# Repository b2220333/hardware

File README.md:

This repository contains information and documentation about the hardware platforms
used and supported in the micro-ROS project.

### Reference hardware platform and development board
The reference hardware platform for the micro-ROS project is the STMicroelectronics
STM32F4 series of microcontrollers. Particularly, the reference development board is the
`Olimex LTD STM32-E407`. More information about this development board can be found in the
[Olimex LTD STM32-E407 instructions](documentation/stm32-e407/stm32-e407.md) file.

### Supporting a new board
TODO: provide instructions on how one should proceed to get a new board supported.

### Other boards (*work in progress (WIP)* )

- **ultra low resources**:
   - STM32VLDISCOVERY (STM32F1)
   - STM32L-DISCOVERY (STM32F4L1)
   - Nucleo-64 (STM32F103)
   - Nucleo-64 (STM32L152)
- **low resources**:
   - *None for now*
- **safety-compliant**:
   - Texas Instruments LAUNCHXL-TMS57004

### License
Unless specified, the content and material available here is open source and
licensed under `<include consortium license>`.

### Conflicts of interest
*The authors declare that there's no conflict of interest in connexion
to the hardware platforms supported or recommended. The same applies to Electronic
Design Automation (EDA) tools and applications used. In addition, the
authors declare that they have not granted, sought, attempted to obtain or accepted
and will not grant, seek, attempt to obtain, or accept any advantage, financial or
in kind, to or from any party whatsoever, constituting an illegal or corrupt practice,
either directly or indirectly, as an incentive or reward relating to the scope of the
work presented in this repository and its relationship with the micro-ROS project.*

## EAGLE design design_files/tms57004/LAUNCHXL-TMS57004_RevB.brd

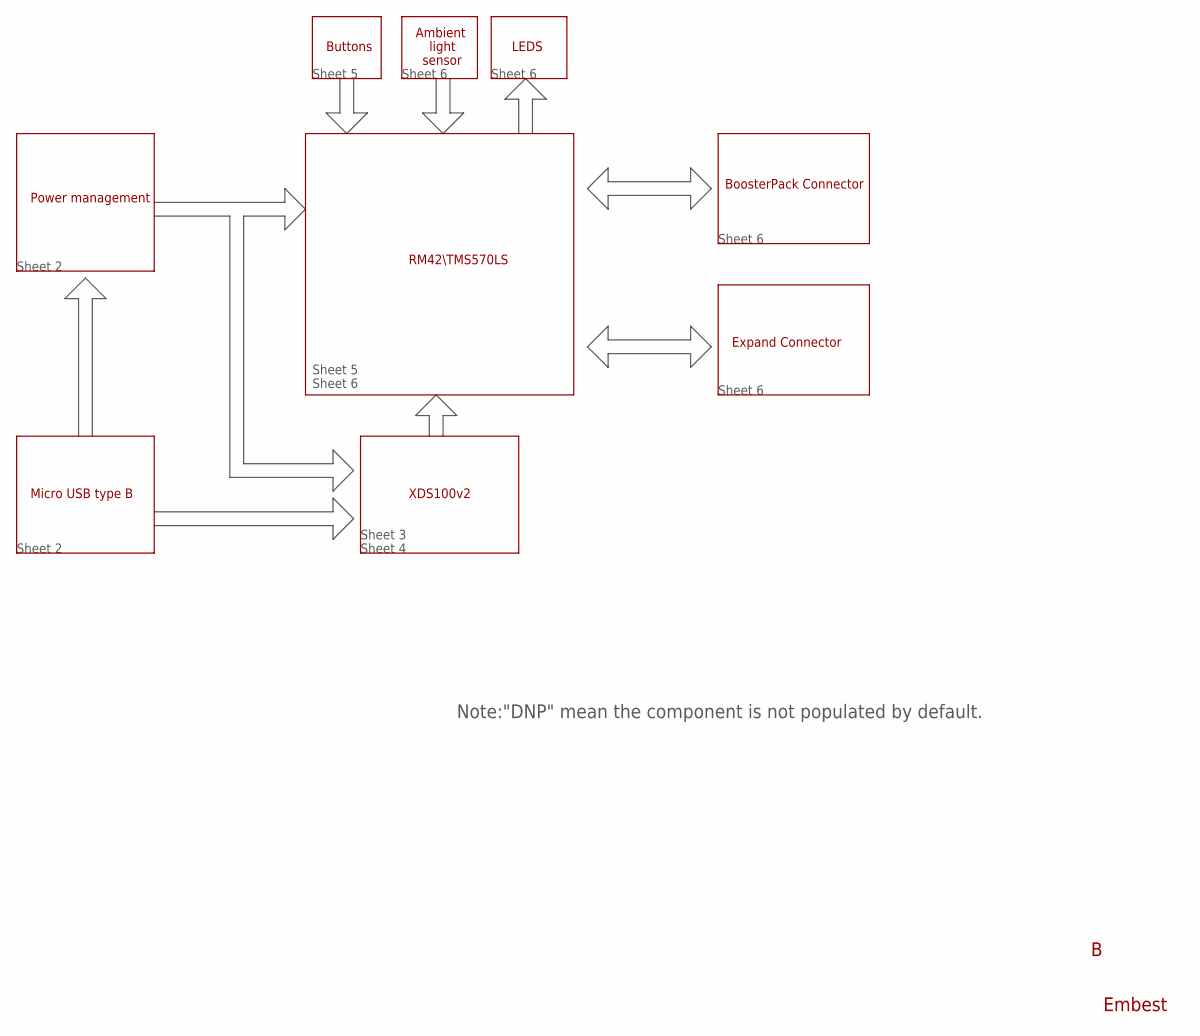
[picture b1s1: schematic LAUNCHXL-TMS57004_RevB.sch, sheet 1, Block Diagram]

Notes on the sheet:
Embest
Power management
Micro USB type B
XDS100v2
RM42\\TMS570LS
BoosterPack Connector
Expand Connector
LEDS
Buttons
Ambient
light
sensor
Note:"DNP" mean the component is not populated by default.
Sheet 2
Sheet 5
Sheet 6
Sheet 3
Sheet 4

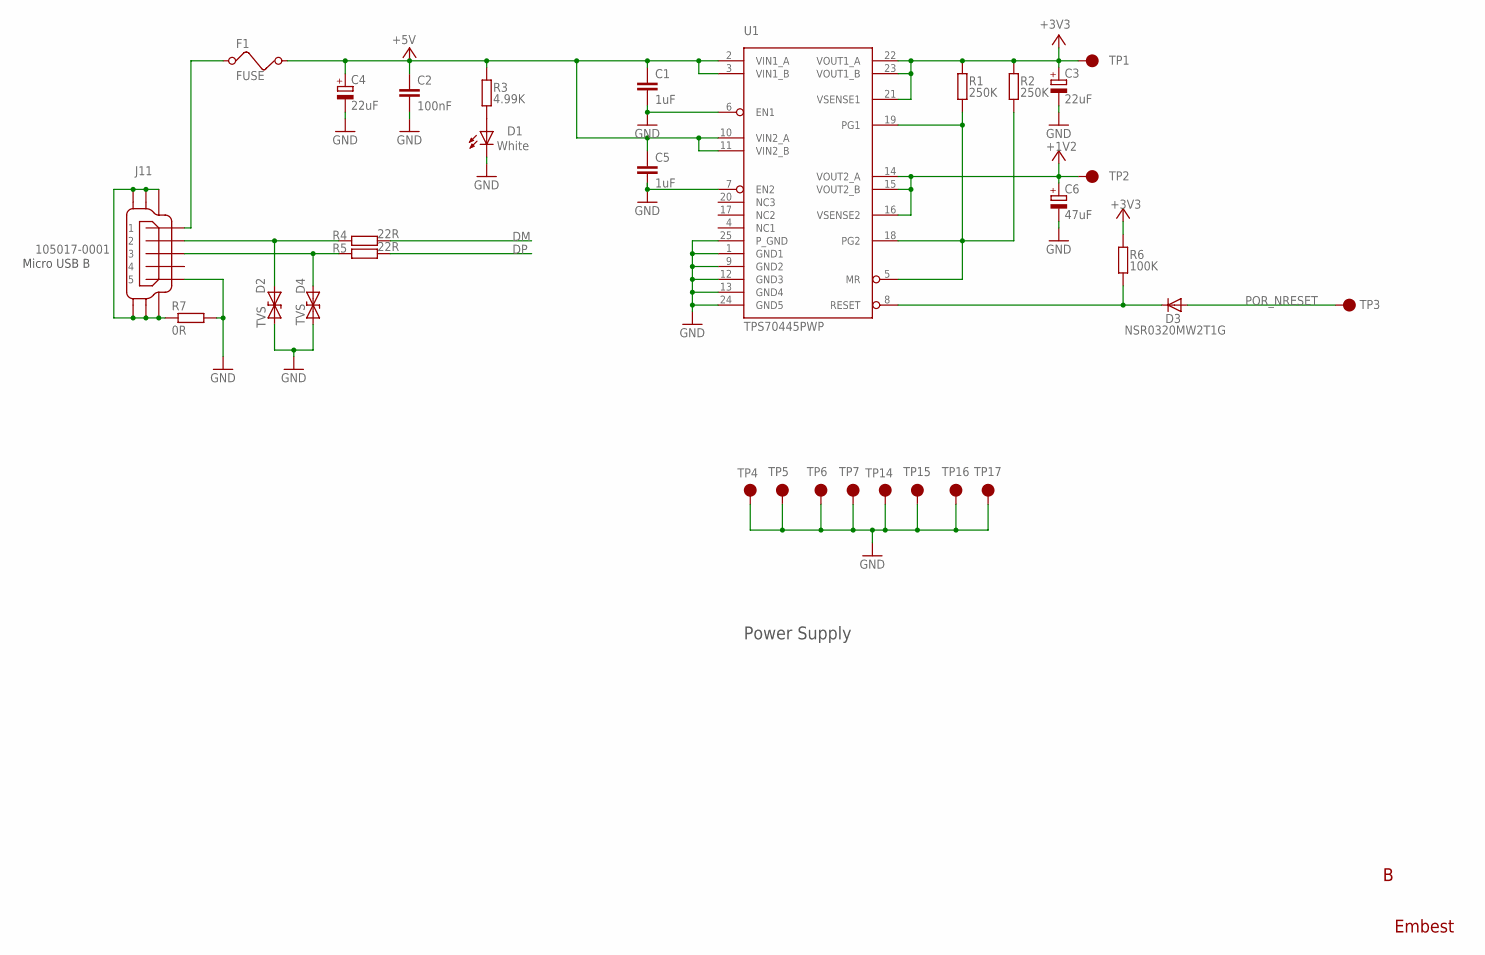
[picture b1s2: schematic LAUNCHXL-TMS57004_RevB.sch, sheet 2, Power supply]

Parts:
C1, C5: 1uF; 0603
C2: 100nF; 0402
C3, C4: 22uF; CT3528
C6: 47uF; CT3528
D1: White; LED0805
D2, D4: TVS; 0402
D3: NSR0320MW2T1G; SOD-323
F1: FUSE; 0805
J11: 105017-0001; MICRO_USB
R1, R2: 250K; 0402
R3: 4.99K; 0402
R4, R5: 22R; 0402
R6: 100K; 0402
R7: 0R; 0603
TP1, TP2, TP3, TP4, TP5, TP6, TP7, TP14, TP15, TP16, TP17: TP
U1: TPS70445PWP; TSSOP24

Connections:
1A: F1.1, J11.1
+3V3: C3.+, R1.2, R2.2, R6.2, TP1.1, U1.21 (VSENSE1), U1.22 (VOUT1_A), U1.23 (VOUT1_B); also elsewhere on the board
+5V: C1.1, C2.1, C4.+, C5.1, F1.2, R3.2, U1.2 (VIN1_A), U1.3 (VIN1_B), U1.10 (VIN2_A), U1.11 (VIN2_B); also elsewhere on the board
DM: R4.1; also elsewhere on the board
DP: R5.1; also elsewhere on the board
GND: C1.2, C2.2, C3.-, C4.-, C5.2, C6.-, D1.C, D2.1, D4.2, J11.5, R7.2, TP4.1, TP5.1, TP6.1, TP7.1, TP14.1, TP15.1, TP16.1, TP17.1, U1.1 (GND1), U1.6 (EN1), U1.7 (EN2), U1.9 (GND2), U1.12 (GND3), U1.13 (GND4), U1.24 (GND5), U1.25 (P_GND); also elsewhere on the board
unnamed: J11.6, J11.7, J11.8, J11.9, J11.10, J11.11, R7.1
unnamed: D2.2, J11.2, R4.2
unnamed: D4.1, J11.3, R5.2
unnamed: D3.C, R6.1, U1.8 (RESET)
unnamed: R1.1, R2.1, U1.5 (MR), U1.18 (PG2), U1.19 (PG1)
unnamed: D1.A, R3.1
POR_NRESET: D3.A, TP3.1; also elsewhere on the board
VCC: C6.+, TP2.1, U1.14 (VOUT2_A), U1.15 (VOUT2_B), U1.16 (VSENSE2); also elsewhere on the board

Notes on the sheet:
Embest
Micro USB B
Power Supply

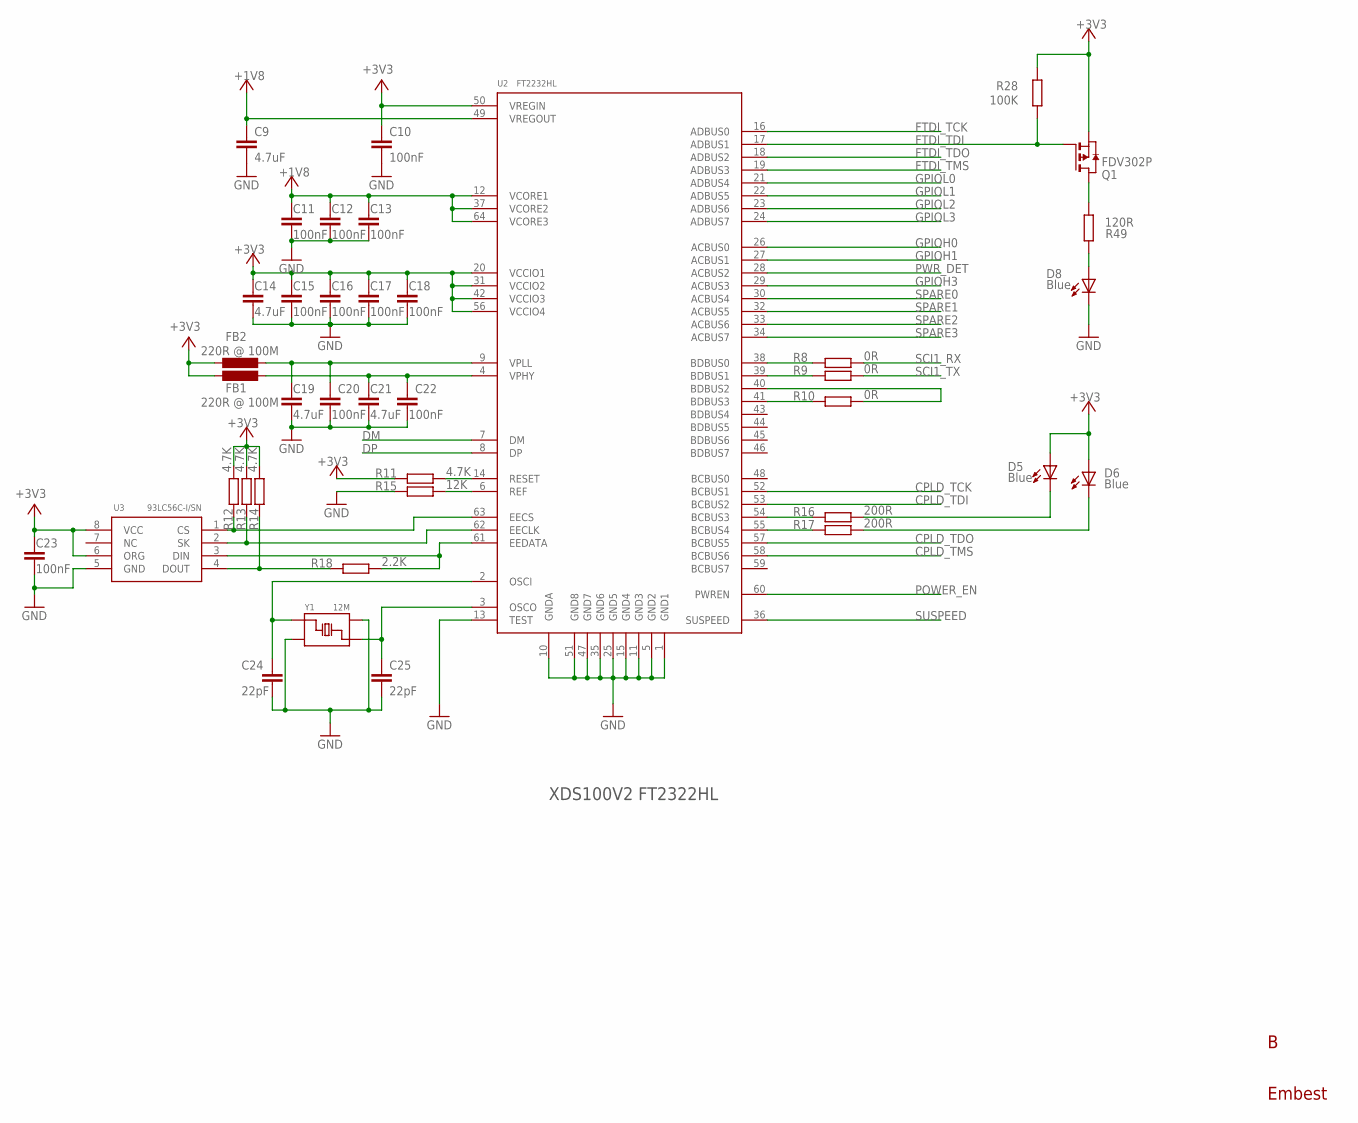
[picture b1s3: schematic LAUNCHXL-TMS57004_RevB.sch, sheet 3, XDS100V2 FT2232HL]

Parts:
C9, C14, C19, C21: 4.7uF; 0805
C10, C11, C12, C13, C15, C16, C17, C18, C20, C22, C23: 100nF; 0402
C24, C25: 22pF; 0402
D5, D6, D8: Blue; LED0805
FB1, FB2: 220R @ 100M; 0805
Q1: FDV302P; SOT-23
R8, R9, R10: 0R; 0402
R11, R12, R13, R14: 4.7K; 0402
R15: 12K; 0402
R16, R17: 200R; 0402
R18: 2.2K; 0402
R28: 100K; 0402
R49: 120R; 0402
U2: FT2232HL; LQFP64
U3: 93LC56C-I/SN; SO8
Y1: 12M; CRYSTAL_3225

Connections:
+1V8: C9.1, C11.1, C12.1, C13.1, U2.12 (VCORE1), U2.37 (VCORE2), U2.49 (VREGOUT), U2.64 (VCORE3); also elsewhere on the board
+3V3: C10.1, C14.1, C15.1, C16.1, C17.1, C18.1, C23.1, D5.A, D6.A, FB1.1, FB2.1, Q1.2 (S), R11.1, R12.2, R13.2, R14.2, R28.2, U2.20 (VCCIO1), U2.31 (VCCIO2), U2.42 (VCCIO3), U2.50 (VREGIN), U2.56 (VCCIO4), U3.6 (ORG), U3.8 (VCC); also elsewhere on the board
CPLD_TCK: U2.52 (BCBUS1); also elsewhere on the board
CPLD_TDI: U2.53 (BCBUS2); also elsewhere on the board
CPLD_TDO: U2.57 (BCBUS5); also elsewhere on the board
CPLD_TMS: U2.58 (BCBUS6); also elsewhere on the board
DM: U2.7 (DM); also elsewhere on the board
DP: U2.8 (DP); also elsewhere on the board
FTDI_TCK: U2.16 (ADBUS0); also elsewhere on the board
FTDI_TDI: Q1.3 (G), R28.1, U2.17 (ADBUS1); also elsewhere on the board
FTDI_TDO: U2.18 (ADBUS2); also elsewhere on the board
FTDI_TMS: U2.19 (ADBUS3); also elsewhere on the board
GND: C9.2, C10.2, C11.2, C12.2, C13.2, C14.2, C15.2, C16.2, C17.2, C18.2, C19.2, C20.2, C21.2, C22.2, C23.2, C24.2, C25.2, D8.C, R15.1, U2.1 (GND1), U2.5 (GND2), U2.10 (GNDA), U2.11 (GND3), U2.13 (TEST), U2.15 (GND4), U2.25 (GND5), U2.35 (GND6), U2.47 (GND7), U2.51 (GND8), U3.5 (GND), Y1.P$2, Y1.P$4; also elsewhere on the board
GPIOH0: U2.26 (ACBUS0); also elsewhere on the board
GPIOH1: U2.27 (ACBUS1); also elsewhere on the board
GPIOH3: U2.29 (ACBUS3); also elsewhere on the board
GPIOL0: U2.21 (ADBUS4); also elsewhere on the board
GPIOL1: U2.22 (ADBUS5); also elsewhere on the board
GPIOL2: U2.23 (ADBUS6); also elsewhere on the board
GPIOL3: U2.24 (ADBUS7); also elsewhere on the board
unnamed: C19.1, C20.1, FB1.2, U2.9 (VPLL)
unnamed: C21.1, C22.1, FB2.2, U2.4 (VPHY)
unnamed: R15.2, U2.6 (REF)
unnamed: R11.2, U2.14 (RESET)
unnamed: C24.1, U2.2 (OSCI), Y1.P$3
unnamed: C25.1, U2.3 (OSCO), Y1.P$1
unnamed: R12.1, U2.63 (EECS), U3.1 (CS)
unnamed: R13.1, U2.62 (EECLK), U3.2 (SK)
unnamed: R18.2, U2.61 (EEDATA), U3.3 (DIN)
unnamed: R14.1, R18.1, U3.4 (DOUT)
unnamed: R8.1, U2.38 (BDBUS0)
unnamed: R9.1, U2.39 (BDBUS1)
unnamed: Q1.1 (D), R49.2
unnamed: D8.A, R49.1
unnamed: R10.2, U2.40 (BDBUS2)
unnamed: R10.1, U2.41 (BDBUS3)
unnamed: D5.C, R16.2
unnamed: D6.C, R17.2
unnamed: R16.1, U2.54 (BCBUS3)
unnamed: R17.1, U2.55 (BCBUS4)
POWER_EN: U2.60 (PWREN); also elsewhere on the board
PWR_DET: U2.28 (ACBUS2); also elsewhere on the board
SCI1_RX: R8.2; also elsewhere on the board
SCI1_TX: R9.2; also elsewhere on the board
SPARE0: U2.30 (ACBUS4); also elsewhere on the board
SPARE1: U2.32 (ACBUS5); also elsewhere on the board
SPARE2: U2.33 (ACBUS6); also elsewhere on the board
SPARE3: U2.34 (ACBUS7); also elsewhere on the board
SUSPEED: U2.36 (SUSPEED); also elsewhere on the board

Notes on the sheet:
Embest
XDS100V2 FT2322HL

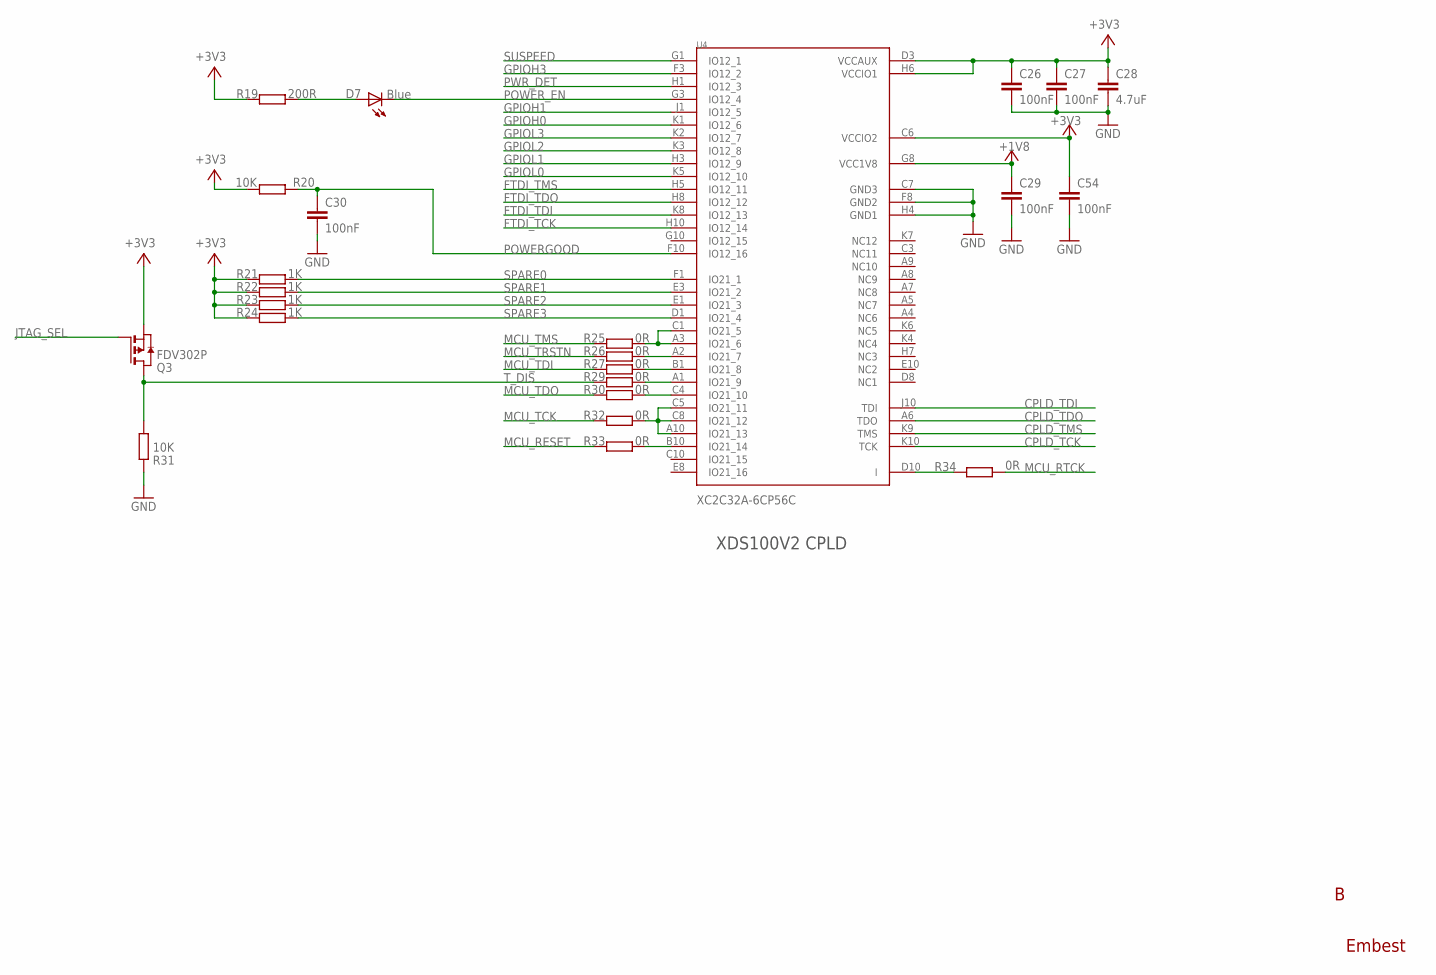
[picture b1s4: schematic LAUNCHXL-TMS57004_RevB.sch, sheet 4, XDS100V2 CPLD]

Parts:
C26, C27, C29, C30, C54: 100nF; 0402
C28: 4.7uF; 0805
D7: Blue; LED0805
Q3: FDV302P; SOT-23
R19: 200R; 0402
R20, R31: 10K; 0402
R21, R22, R23, R24: 1K; 0402
R25, R26, R27, R29, R30, R32, R33, R34: 0R; 0402
U4: XC2C32A-6CP56C; CP56

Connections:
+1V8: C29.1, U4.G8 (VCC1V8); also elsewhere on the board
+3V3: C26.1, C27.1, C28.1, C54.1, Q3.2 (S), R19.1, R20.2, R21.1, R22.1, R23.1, R24.1, U4.C6 (VCCIO2), U4.D3 (VCCAUX), U4.H6 (VCCIO1); also elsewhere on the board
CPLD_TCK: U4.K10 (TCK); also elsewhere on the board
CPLD_TDI: U4.J10 (TDI); also elsewhere on the board
CPLD_TDO: U4.A6 (TDO); also elsewhere on the board
CPLD_TMS: U4.K9 (TMS); also elsewhere on the board
FTDI_TCK: U4.H10 (IO12_14); also elsewhere on the board
FTDI_TDI: U4.K8 (IO12_13); also elsewhere on the board
FTDI_TDO: U4.H8 (IO12_12); also elsewhere on the board
FTDI_TMS: U4.H5 (IO12_11); also elsewhere on the board
GND: C26.2, C27.2, C28.2, C29.2, C30.2, C54.2, R31.1, U4.C7 (GND3), U4.F8 (GND2), U4.H4 (GND1); also elsewhere on the board
GPIOH0: U4.K1 (IO12_6); also elsewhere on the board
GPIOH1: U4.J1 (IO12_5); also elsewhere on the board
GPIOH3: U4.F3 (IO12_2); also elsewhere on the board
GPIOL0: U4.K5 (IO12_10); also elsewhere on the board
GPIOL1: U4.H3 (IO12_9); also elsewhere on the board
GPIOL2: U4.K3 (IO12_8); also elsewhere on the board
GPIOL3: U4.K2 (IO12_7); also elsewhere on the board
JTAG_SEL: Q3.3 (G); also elsewhere on the board
MCU_RESET: R33.1; also elsewhere on the board
MCU_RTCK: R34.2; also elsewhere on the board
MCU_TCK: R32.1; also elsewhere on the board
MCU_TDI: R27.1; also elsewhere on the board
MCU_TDO: R30.1; also elsewhere on the board
MCU_TMS: R25.1; also elsewhere on the board
MCU_TRSTN: R26.1; also elsewhere on the board
unnamed: D7.A, R19.2
unnamed: R25.2, U4.A3 (IO21_6), U4.C1 (IO21_5)
unnamed: R26.2, U4.A2 (IO21_7)
unnamed: R27.2, U4.B1 (IO21_8)
unnamed: R29.2, U4.A1 (IO21_9)
unnamed: R30.2, U4.C4 (IO21_10)
unnamed: R32.2, U4.A10 (IO21_13), U4.C5 (IO21_11), U4.C8 (IO21_12)
unnamed: R33.2, U4.B10 (IO21_14)
unnamed: R34.1, U4.D10 (I)
POWERGOOD: C30.1, R20.1, U4.F10 (IO12_16)
POWER_EN: D7.C, U4.G3 (IO12_4); also elsewhere on the board
PWR_DET: U4.H1 (IO12_3); also elsewhere on the board
SPARE0: R21.2, U4.F1 (IO21_1); also elsewhere on the board
SPARE1: R22.2, U4.E3 (IO21_2); also elsewhere on the board
SPARE2: R23.2, U4.E1 (IO21_3); also elsewhere on the board
SPARE3: R24.2, U4.D1 (IO21_4); also elsewhere on the board
SUSPEED: U4.G1 (IO12_1); also elsewhere on the board
T_DIS: Q3.1 (D), R29.1, R31.2

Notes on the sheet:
Embest
XDS100V2 CPLD

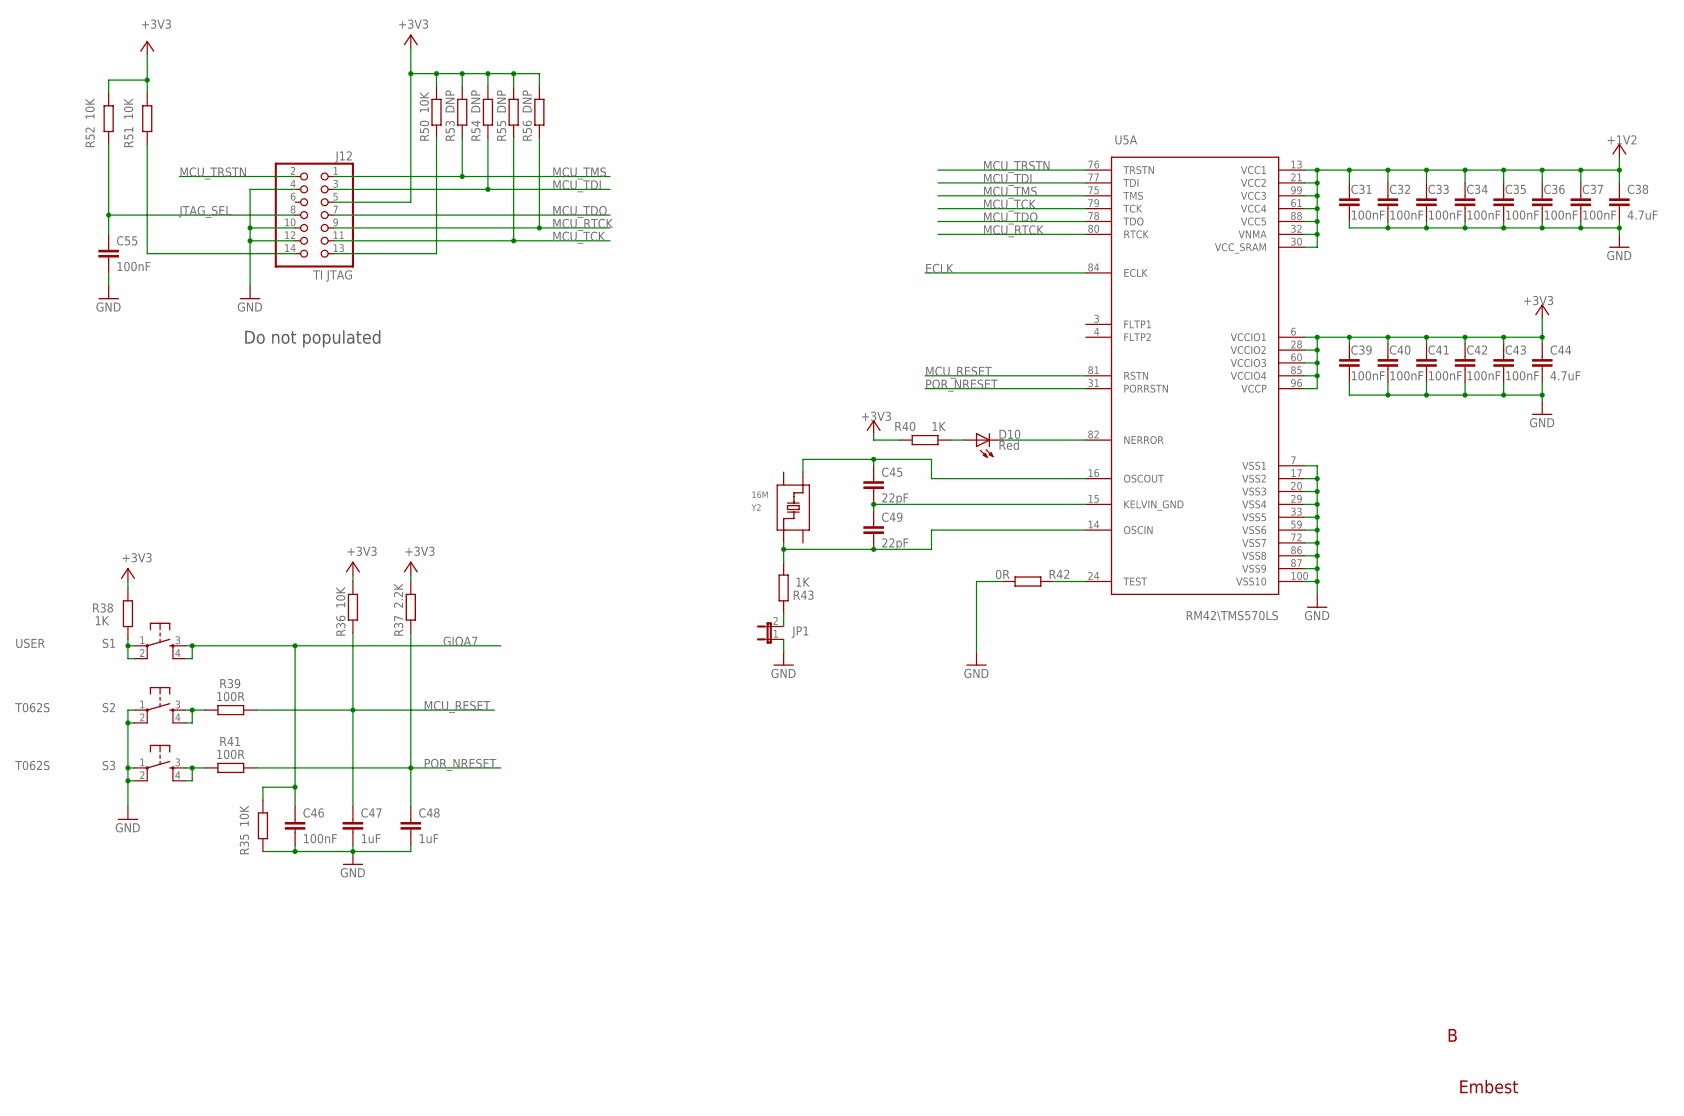
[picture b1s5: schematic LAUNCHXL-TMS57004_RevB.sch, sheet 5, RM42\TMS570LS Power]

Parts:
C31, C32, C33, C34, C35, C36, C37, C39, C40, C41, C42, C43, C46, C55: 100nF; 0402
C38, C44: 4.7uF; 0805
C45, C49: 22pF; 0402
C47, C48: 1uF; 0603
D10: Red; LED0805
J12: TI JTAG; BOXCONNECT2X7
JP1: JUMPER-2.54
R35, R36, R50, R51, R52: 10K; 0402
R37: 2.2K; 0402
R38, R40, R43: 1K; 0402
R39, R41: 100R; 0402
R42: 0R; 0402
R53, R54, R55, R56: DNP; 0402
S1: USER; T062S
S2, S3: T062S
U5: RM42\\TMS570LS; LQFP100
Y2: 16M; CRYSTAL_3225

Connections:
+3V3: C39.1, C40.1, C41.1, C42.1, C43.1, C44.1, J12.5, R36.2, R37.2, R38.1, R40.2, R50.2, R51.2, R52.2, R53.2, R54.2, R55.2, R56.2, U5.6 (VCCIO1), U5.28 (VCCIO2), U5.60 (VCCIO3), U5.85 (VCCIO4), U5.96 (VCCP); also elsewhere on the board
ECLK: U5.84 (ECLK); also elsewhere on the board
GIOA7: C46.1, R35.2, S1.3, S1.4; also elsewhere on the board
GND: C31.2, C32.2, C33.2, C34.2, C35.2, C36.2, C37.2, C38.2, C39.2, C40.2, C41.2, C42.2, C43.2, C44.2, C46.2, C47.2, C48.2, C55.2, J12.4, J12.10, J12.12, JP1.1, R35.1, R42.2, S2.1, S2.2, S3.1, S3.2, U5.7 (VSS1), U5.17 (VSS2), U5.20 (VSS3), U5.29 (VSS4), U5.33 (VSS5), U5.59 (VSS6), U5.72 (VSS7), U5.86 (VSS8), U5.87 (VSS9), U5.100 (VSS10); also elsewhere on the board
JTAG_SEL: C55.1, J12.8, R52.1; also elsewhere on the board
MCU_RESET: C47.1, R36.1, R39.1, U5.81 (RSTN); also elsewhere on the board
MCU_RTCK: J12.9, R56.1, U5.80 (RTCK); also elsewhere on the board
MCU_TCK: J12.11, R55.1, U5.79 (TCK); also elsewhere on the board
MCU_TDI: J12.3, R54.1, U5.77 (TDI); also elsewhere on the board
MCU_TDO: J12.7, U5.78 (TDO); also elsewhere on the board
MCU_TMS: J12.1, R53.1, U5.75 (TMS); also elsewhere on the board
MCU_TRSTN: J12.2, U5.76 (TRSTN); also elsewhere on the board
unnamed: R38.2, S1.1, S1.2
unnamed: JP1.2, R43.2
unnamed: R42.1, U5.24 (TEST)
unnamed: J12.14, R51.1
unnamed: D10.A, R40.1
unnamed: C49.2, R43.1, U5.14 (OSCIN), Y2.P$3
unnamed: C45.2, C49.1, U5.15 (KELVIN_GND)
unnamed: C45.1, U5.16 (OSCOUT), Y2.P$1
unnamed: R39.2, S2.3, S2.4
unnamed: R41.2, S3.3, S3.4
unnamed: J12.13, R50.1
POR_NRESET: C48.1, R37.1, R41.1, U5.31 (PORRSTN); also elsewhere on the board
POWER_EN1: D10.C, U5.82 (NERROR)
VCC: C31.1, C32.1, C33.1, C34.1, C35.1, C36.1, C37.1, C38.1, U5.13 (VCC1), U5.21 (VCC2), U5.30 (VCC_SRAM), U5.32 (VNMA), U5.61 (VCC4), U5.88 (VCC5), U5.99 (VCC3); also elsewhere on the board

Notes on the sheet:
Embest
Do not populated

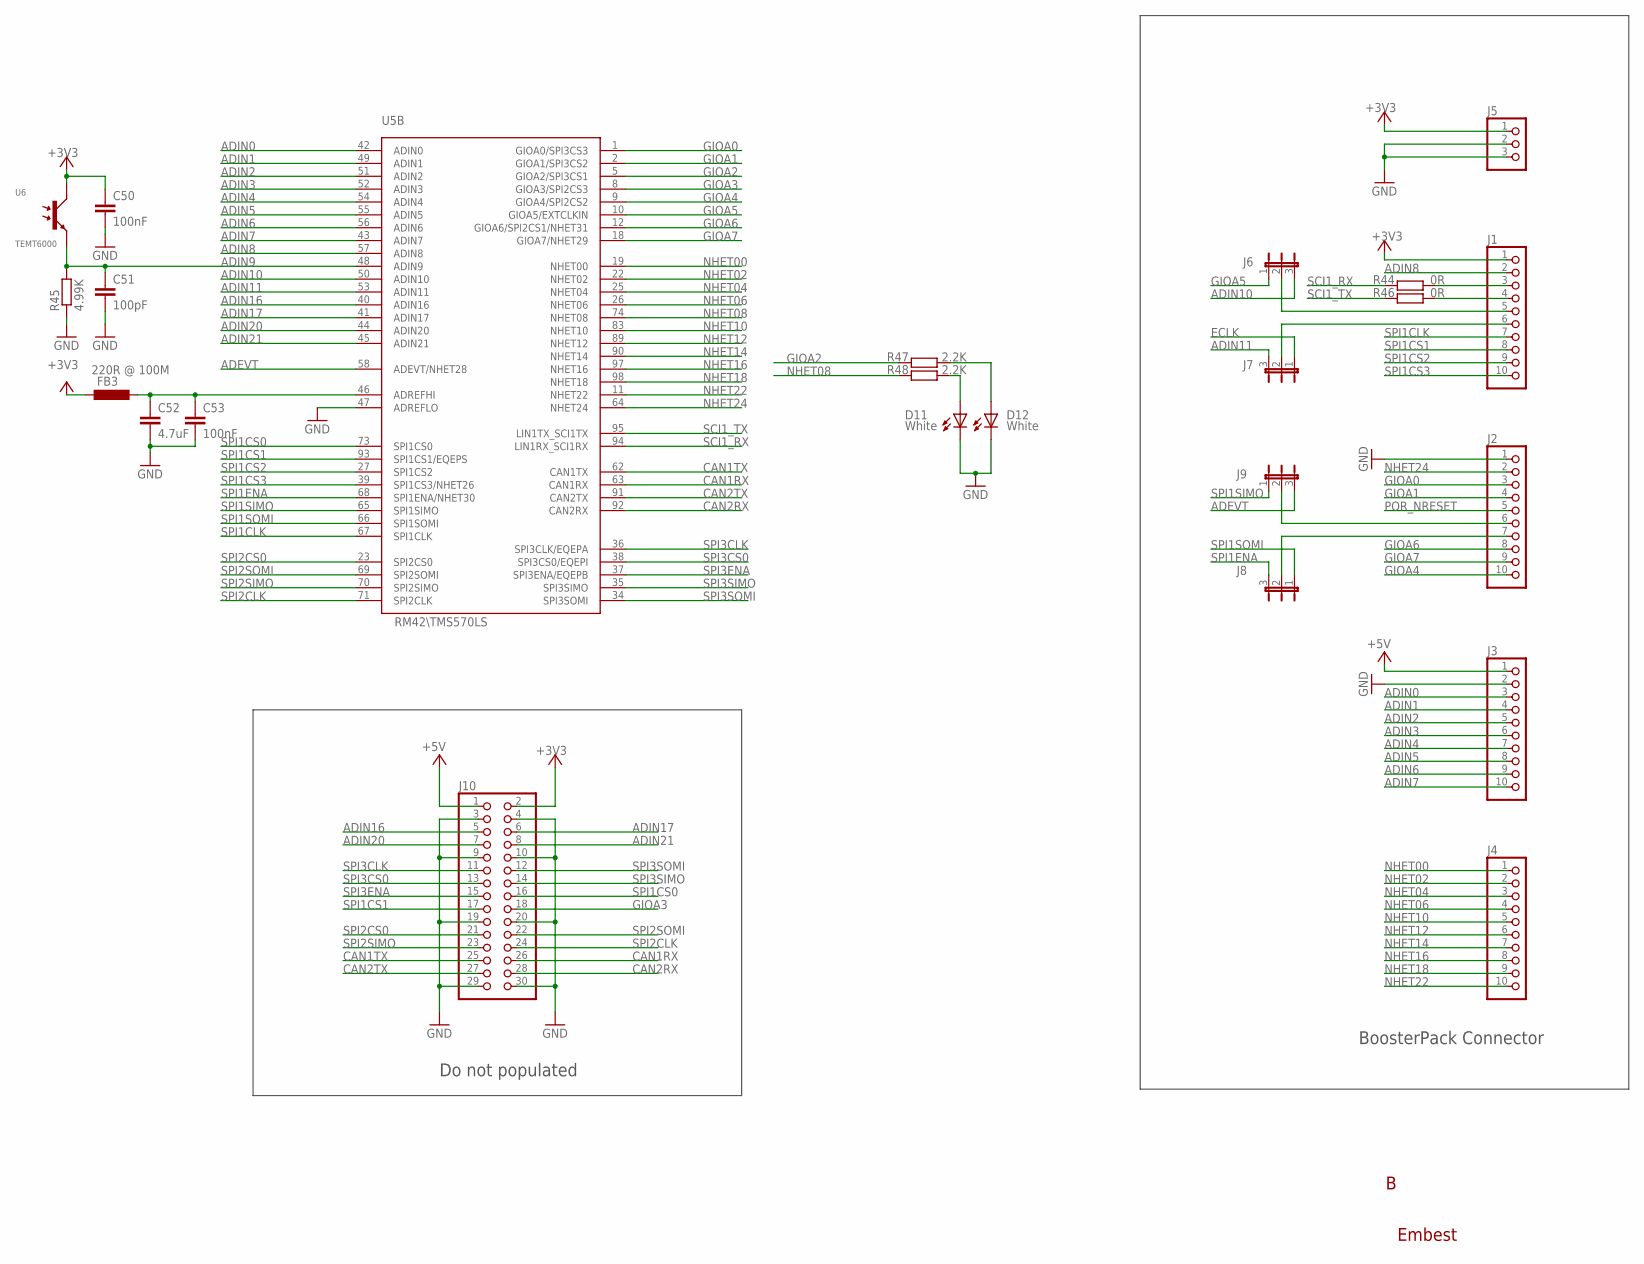
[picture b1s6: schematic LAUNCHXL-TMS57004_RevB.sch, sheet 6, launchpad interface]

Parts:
C50, C53: 100nF; 0402
C51: 100pF; 0402
C52: 4.7uF; 0805
D11, D12: White; LED0805
FB3: 220R @ 100M; 0805
J1, J2, J3, J4: PINHEAFER1X10
J5: PINHEADER1X3
J6, J7, J8, J9: HEADER3-100
J10: 2X15
R44, R46: 0R; 0402
R45: 4.99K; 0402
R47, R48: 2.2K; 0402
U5: RM42\\TMS570LS; LQFP100
U6: TEMT6000

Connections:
+3V3: C50.1, FB3.1, J1.1, J5.1, J10.2, U6.3 (C); also elsewhere on the board
+5V: J3.1, J10.1; also elsewhere on the board
ADEVT: J9.3, U5.58 (ADEVT/NHET28)
ADIN0: J3.3, U5.42 (ADIN0)
ADIN1: J3.4, U5.49 (ADIN1)
ADIN2: J3.5, U5.51 (ADIN2)
ADIN3: J3.6, U5.52 (ADIN3)
ADIN4: J3.7, U5.54 (ADIN4)
ADIN5: J3.8, U5.55 (ADIN5)
ADIN6: J3.9, U5.56 (ADIN6)
ADIN7: J3.10, U5.43 (ADIN7)
ADIN8: J1.2, U5.57 (ADIN8)
ADIN9: C51.1, R45.2, U5.48 (ADIN9), U6.1 (E)
ADIN10: J6.3, U5.50 (ADIN10)
ADIN11: J7.3, U5.53 (ADIN11)
ADIN16: J10.5, U5.40 (ADIN16)
ADIN17: J10.6, U5.41 (ADIN17)
ADIN20: J10.7, U5.44 (ADIN20)
ADIN21: J10.8, U5.45 (ADIN21)
CAN1RX: J10.26, U5.63 (CAN1RX)
CAN1TX: J10.25, U5.62 (CAN1TX)
CAN2RX: J10.28, U5.92 (CAN2RX)
CAN2TX: J10.27, U5.91 (CAN2TX)
ECLK: J7.1; also elsewhere on the board
GIOA0: J2.3, U5.1 (GIOA0/SPI3CS3)
GIOA1: J2.4, U5.2 (GIOA1/SPI3CS2)
GIOA2: R47.2, U5.5 (GIOA2/SPI3CS1)
GIOA3: J10.18, U5.8 (GIOA3/SPI2CS3)
GIOA4: J2.10, U5.9 (GIOA4/SPI2CS2)
GIOA5: J6.1, U5.10 (GIOA5/EXTCLKIN)
GIOA6: J2.8, U5.12 (GIOA6/SPI2CS1/NHET31)
GIOA7: J2.9, U5.18 (GIOA7/NHET29); also elsewhere on the board
GND: C50.2, C51.2, C52.2, C53.2, D11.C, D12.C, J2.1, J3.2, J5.2, J5.3, J10.3, J10.4, J10.9, J10.10, J10.19, J10.20, J10.29, J10.30, R45.1, U5.47 (ADREFLO); also elsewhere on the board
unnamed: C52.1, C53.1, FB3.2, U5.46 (ADREFHI)
unnamed: J1.5, J6.2
unnamed: D11.A, R48.1
unnamed: J1.6, J7.2
unnamed: D12.A, R47.1
unnamed: J1.3, R44.1
unnamed: J1.4, R46.1
unnamed: J2.6, J9.2
unnamed: J2.7, J8.2
NHET00: J4.1, U5.19 (NHET00)
NHET02: J4.2, U5.22 (NHET02)
NHET04: J4.3, U5.25 (NHET04)
NHET06: J4.4, U5.26 (NHET06)
NHET08: R48.2, U5.74 (NHET08)
NHET10: J4.5, U5.83 (NHET10)
NHET12: J4.6, U5.89 (NHET12)
NHET14: J4.7, U5.90 (NHET14)
NHET16: J4.8, U5.97 (NHET16)
NHET18: J4.9, U5.98 (NHET18)
NHET22: J4.10, U5.11 (NHET22)
NHET24: J2.2, U5.64 (NHET24)
POR_NRESET: J2.5; also elsewhere on the board
SCI1_RX: R44.2, U5.94 (LIN1RX_SCI1RX); also elsewhere on the board
SCI1_TX: R46.2, U5.95 (LIN1TX_SCI1TX); also elsewhere on the board
SPI1CLK: J1.7, U5.67 (SPI1CLK)
SPI1CS0: J10.16, U5.73 (SPI1CS0)
SPI1CS1: J1.8, J10.17, U5.93 (SPI1CS1/EQEPS)
SPI1CS2: J1.9, U5.27 (SPI1CS2)
SPI1CS3: J1.10, U5.39 (SPI1CS3/NHET26)
SPI1ENA: J8.3, U5.68 (SPI1ENA/NHET30)
SPI1SIMO: J9.1, U5.65 (SPI1SIMO)
SPI1SOMI: J8.1, U5.66 (SPI1SOMI)
SPI2CLK: J10.24, U5.71 (SPI2CLK)
SPI2CS0: J10.21, U5.23 (SPI2CS0)
SPI2SIMO: J10.23, U5.70 (SPI2SIMO)
SPI2SOMI: J10.22, U5.69 (SPI2SOMI)
SPI3CLK: J10.11, U5.36 (SPI3CLK/EQEPA)
SPI3CS0: J10.13, U5.38 (SPI3CS0/EQEPI)
SPI3ENA: J10.15, U5.37 (SPI3ENA/EQEPB)
SPI3SIMO: J10.14, U5.35 (SPI3SIMO)
SPI3SOMI: J10.12, U5.34 (SPI3SOMI)

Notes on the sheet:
Embest
BoosterPack Connector
Do not populated

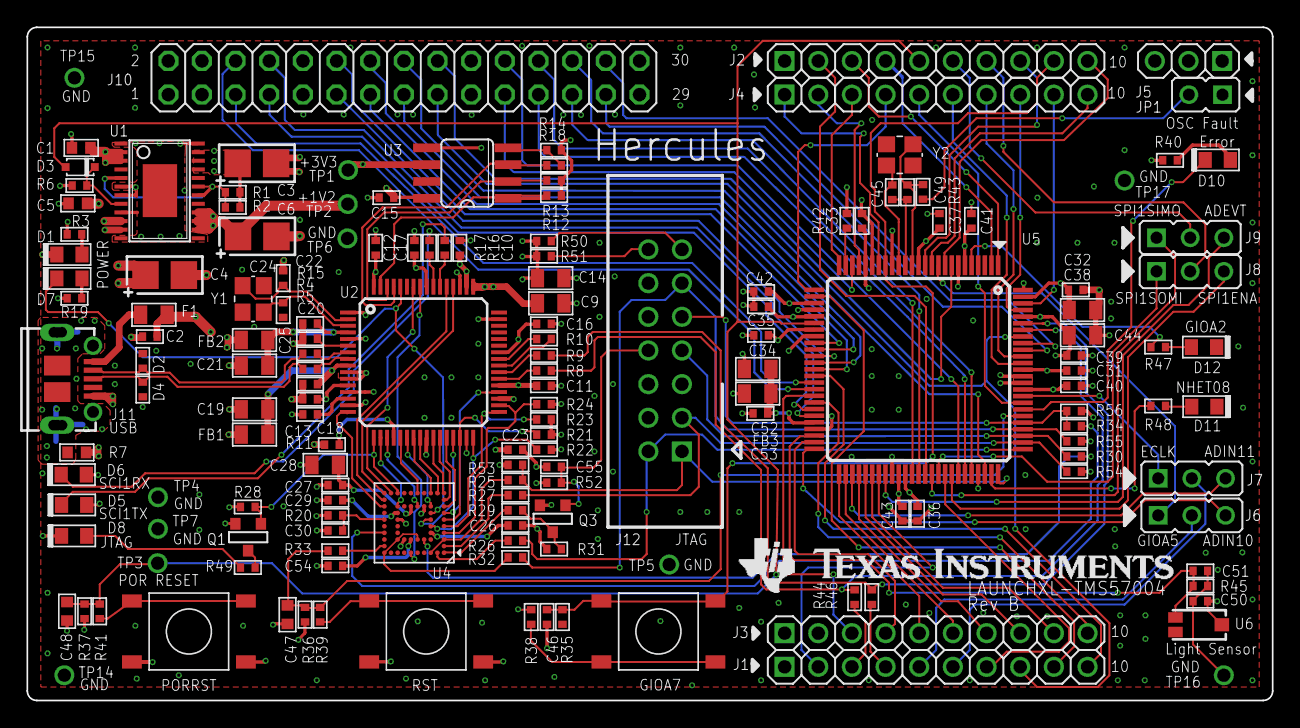
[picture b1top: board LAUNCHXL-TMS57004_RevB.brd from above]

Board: 4 copper layers, 94.0 x 50.8 mm, 162 parts (0 on the bottom side), 158 nets.

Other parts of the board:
U$1: TI_HORZ

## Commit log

2018-02-21 First commit, add some structure in the repo
2018-02-21 Add a few bits for the reference dev. board
2018-02-21 Link dev. env. setup process
2018-02-21 Adding the documentaion of STM32L1Discovery board
2018-02-21 Solving a mistake in the name of the board
2018-02-21 The name of the image was wrong
2018-02-21 Changing the name
2018-02-21 Adding the schematic pdf of the board
2018-02-21 Adding the documentation of the TMS57004 board
2018-02-21 Modification on .md file
2018-02-22 Modification of the documentation file
2018-02-23 Update stm32-e407.md
    Add I2C NuttX guide
2018-02-23 Update stm32l1discovery.md
    Add I2C NuttX guide
2018-02-23 Update tms57004.md
    Add I2C NuttX guide.
2018-02-23 Update stm32l1discovery.md
    Add App development guide
2018-02-23 Update stm32-e407.md
    Add App developing guide
2018-02-27 Add Ethernet guide.

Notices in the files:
parts and their libraries:
SparkFun: Licensing: CC v3.0 Share-Alike You are welcome to use this library for commercial purposes.
